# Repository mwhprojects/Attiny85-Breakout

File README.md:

# ATtiny85 Breakout Board
Eagle board and schematic files for a breakout of the ATtiny85 microcontroller. It is designed for people who want to use an Arduino to program the ATtiny85 uC. It makes it easier by having pins specifically labelled to connect it to an Arduino for programming.

Currently available on Tindie: https://www.tindie.com/products/mwhelectronics/attiny85-programmer-and-breakout-board-2/

## License Information
<br />This work is licensed under a <a rel="license" href="http://creativecommons.org/licenses/by-sa/4.0/">Creative Commons Attribution-ShareAlike 4.0 International License</a>.

Distributed as-is; no warranty is given.

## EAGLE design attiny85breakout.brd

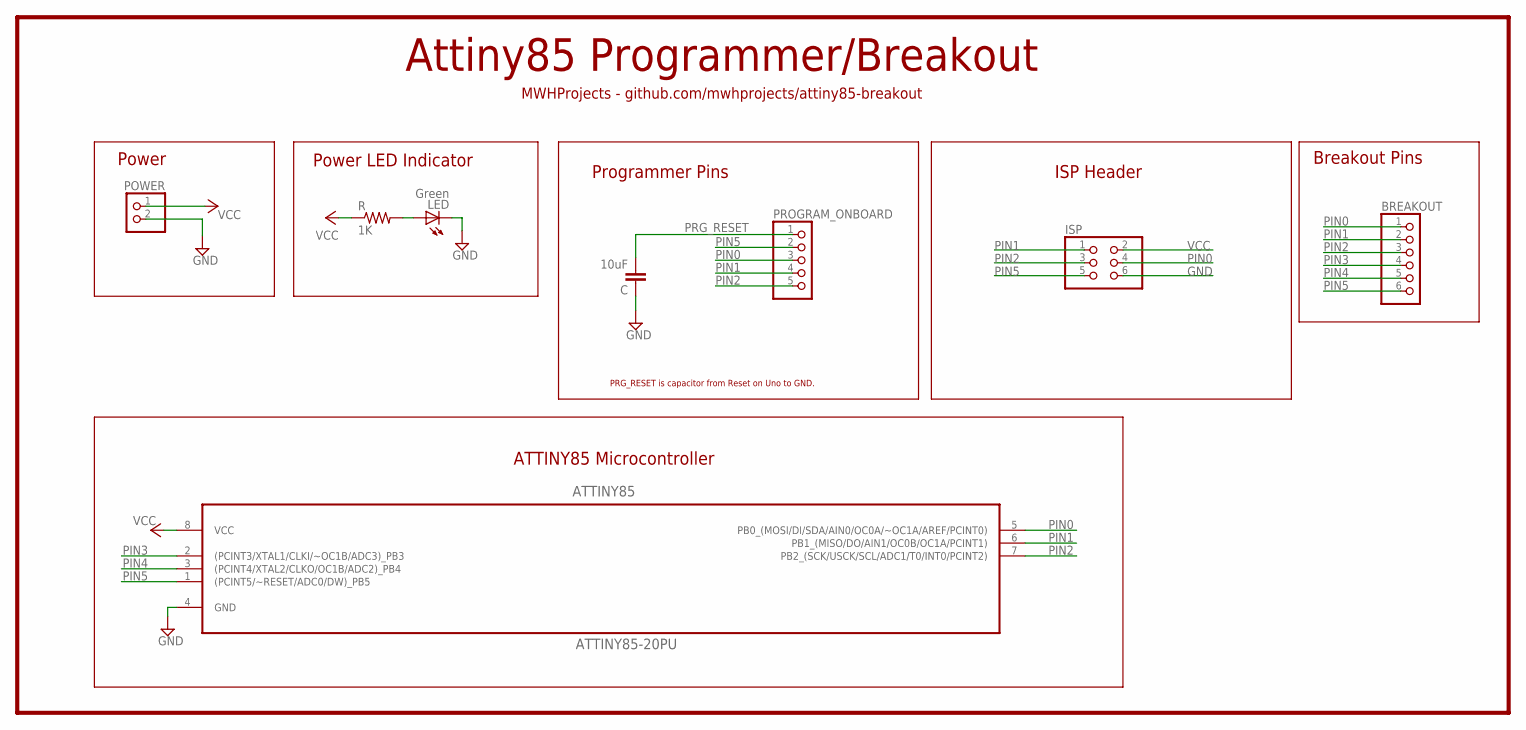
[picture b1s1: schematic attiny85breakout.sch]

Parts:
ATTINY85: ATTINY85-20PU; DIP254P762X533-8
BREAKOUT: 0; 1X06
C: 10uF; C0805
ISP: PINHD-2X3; 2X03
LED: Green; CHIP-LED0805
POWER: 0; 1X02
PROGRAM_ONBOARD: 0; 1X05
R: 1K; R0805

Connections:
GND: ATTINY85.4 (GND), C.1, ISP.6, LED.C, POWER.2
unnamed: LED.A, R.2
PIN0: ATTINY85.5 (PB0_(MOSI/DI/SDA/AIN0/OC0A/~OC1A/AREF/P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), BREAKOUT.1, ISP.4, PROGRAM_ONBOARD.3
PIN1: ATTINY85.6 (PB1_(MISO/DO/AIN1/OC0B/OC1A/PCINT1)), BREAKOUT.2, ISP.1, PROGRAM_ONBOARD.4
PIN2: ATTINY85.7 (PB2_(SCK/USCK/SCL/ADC1/T0/INT0/PCINT2)), BREAKOUT.3, ISP.3, PROGRAM_ONBOARD.5
PIN3: ATTINY85.2 ((PCINT3/XTAL1/CLKI/~OC1B/ADC3)_PB3), BREAKOUT.4
PIN4: ATTINY85.3 ((PCINT4/XTAL2/CLKO/OC1B/ADC2)_PB4), BREAKOUT.5
PIN5: ATTINY85.1 ((PCINT5/~RESET/ADC0/DW)_PB5), BREAKOUT.6, ISP.5, PROGRAM_ONBOARD.2
PRG_RESET: C.2, PROGRAM_ONBOARD.1
VCC: ATTINY85.8 (VCC), ISP.2, POWER.1, R.1

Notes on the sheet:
Attiny85 Programmer/Breakout
Power
Power LED Indicator
Programmer Pins
Breakout Pins
ATTINY85 Microcontroller
PRG_RESET is capacitor from Reset on Uno to GND.
MWHProjects - github.com/mwhprojects/attiny85-breakout
ISP Header

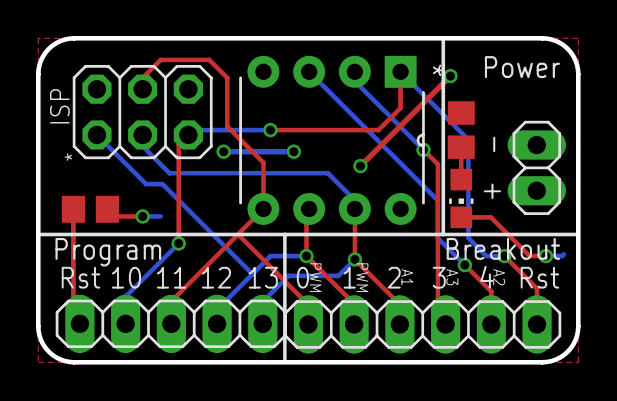
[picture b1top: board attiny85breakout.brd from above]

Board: 2 copper layers, 30.0 x 18.0 mm, 8 parts (0 on the bottom side), 10 nets.

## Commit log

2015-05-09 :space_invader: Added .gitattributes & .gitignore files
2015-05-09 Initial Release
    Have at it!
